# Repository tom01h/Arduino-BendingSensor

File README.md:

# ひずみゲージでスキー板のたわみを測る

[Arduino UNO R4もどきのボードと自作基板](https://github.com/tom01h/RA4M1)を使って実験します

事情あって、センサー部分は実際にスキー場で使っているものですが、制御部分はスキー場で使っているものとは別のものです

センサー部分は[ひずみゲージ](https://ja.aliexpress.com/item/1005003672107724.html)（BX120-100AA）と[HX711](https://ja.aliexpress.com/item/1005004245273524.html)（Mini Board）をちょい変(3.3V化)したものを使います

## Arduinoもどき

制御には[Arduino UNO R4もどきのボードと自作基板](https://github.com/tom01h/RA4M1)を使います

D5端子がクロック、D2,D3,D4端子がデータ入力端子です

プログラムは`BendingSensor.ino`です  
LCDに計測値を表示するためにu8g2ライブラリを使います

1秒に10回計測値を表示、最初の10回はゼロキャリブレーションに使います

### ピン配置
下の絵ではJ5,J9がDATA0(D4)で、絵には無いけどJ10,J11がDATA1(D3)でJ15,J16がDATA2(D2)です  
それぞれ、どちらか一方のコネクタを使います

## センサー

### HX711を改造する
3.3Vに対応するために[ここ](https://kohacraft.com/archives/202103201133.html)の真似をして改造します  
(合成抵抗違うくね？って気はしますが…)  
とっても細かい作業です

2個のひずみゲージと組み合わせてホイートストンブリッジを作るための基板が`hx711.kicad_XX`です  
切り取って使います  
0.8mm厚で作りました  
あまり良くないと言われている基板同士のはんだ付け

### 回路
(E+)-(A+)間にひずみゲージを表向きに、(E+)-(A-)間にひずみゲージを裏向きに、(A+)-(E-)と(A-)-(E-)間は固定の抵抗(120Ω)をつなぎます  
2枚使っているのは温度補償のため  
スキー板の表裏に貼るわけにもいかないので、間に挟んだ0.4mm厚のプラバンに瞬間接着剤で固定しています  
それ以外の部分は大体でついていればよいので両面テープで固定しています

### 設計図（のようなもの）
断面図

センサー部分は上から
- 100mm x 15mm のプラバン（0.4mm厚）
- 両面テープ
- ひずみゲージ（表）
- 瞬間接着剤
- 100mm x 15mm のプラバン（0.4mm厚）
- 瞬間接着剤
- ひずみゲージ（裏）
- 両面テープ
- 135mm x 15mm のプラバン（0.4mm厚）

HX711をプラバンに止めているのは1.2mm厚の両面テープ

センサー部分の平面図

### 組み立て
古い写真です
#### センサー部分

#### センサーとHX711接続
下の写真はHX711基板は裏返った状態

#### ケーブルの加工

4芯のケーブルは[これ](https://ja.aliexpress.com/item/4000570401041.html)の`AWG28 4Core`を使っているのだけど、ちょっと固すぎな気がします  
センサー（HX711）側は外皮（黒いの）2㎝だけむいて、中の線は5mmだけむいています  
外皮をむくのには[これ](https://ja.aliexpress.com/item/1005005504458064.html)を使っています  

制御基板側は長めに外皮（黒いの）をむいて、熱収縮チューブで保護しています  
コネクタは[これ](https://ja.aliexpress.com/item/1005003757087073.html)の4P  
Groveコネクタっぽい見た目ですが、電源とGNDを逆にするという致命的な間違いをしています。今更直せないのでこのままいきますが…  

#### ケーブルに接続
1枚目が表から見た絵で2枚目が裏から見た絵

#### ホットボンド

#### 熱収縮チューブ

長さ16㎝に切った直径12mmの[熱収縮チューブ](https://ja.aliexpress.com/item/32838965930.html)`12mm`を全体の保護に使います  
アイロンで加熱しますが、加熱しすぎに注意！！

↑をチューブでくるむと↓になる

## 後処理

実際にスキー場で使うとノイズとドリフトがひどいのでバンドパスフィルターで後処理します  
後処理でドリフト消すなら温度補償いらなかったのでは？とも思いますが…

```
import numpy as np
from scipy import signal
from scipy import stats

略

    #バターワースフィルタ（バンドパス）
    def bandpass(x, samplerate, fp, fs, gpass, gstop):
        fn = samplerate / 2                               #ナイキスト周波数
        wp = fp / fn                                      #ナイキスト周波数で通過域端周波数を正規化
        ws = fs / fn                                      #ナイキスト周波数で阻止域端周波数を正規化
        N, Wn = signal.buttord(wp, ws, gpass, gstop)      #オーダーとバターワースの正規化周波数を計算
        b, a = signal.butter(N, Wn, "band")               #フィルタ伝達関数の分子と分母を計算
        y = signal.filtfilt(b, a, x)                      #信号に対してフィルタをかける
        return y

略

    samplerate = 10
    gpass = 3    #通過域端最大損失[dB]
    gstop = 40   #阻止域端最小損失[dB]

    # バンドパス
    fp = np.array([0.06, 2])   # 通過域端周波数[Hz]
    fs = np.array([0.03, 4])   # 阻止域端周波数[Hz]
    for i in range(6):
        x=y[i]
        y[i] = bandpass(x, samplerate, fp, fs, gpass, gstop)

    # 正規化
    for i in range(6):
        x=y[i]
        y[i] = stats.zscore(x)
```

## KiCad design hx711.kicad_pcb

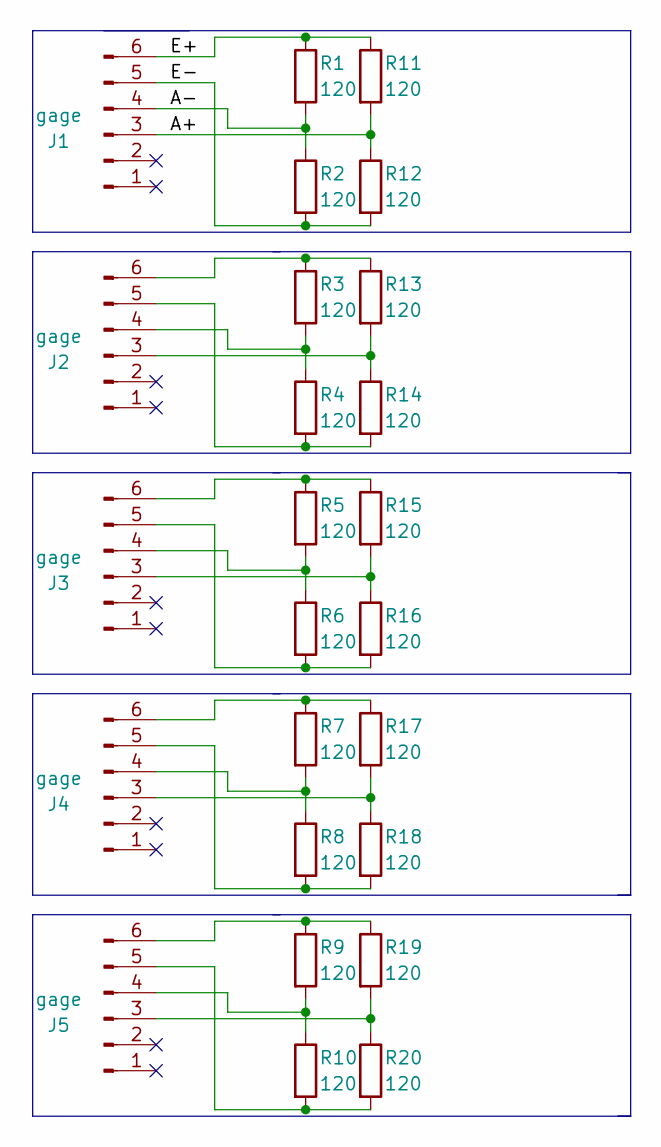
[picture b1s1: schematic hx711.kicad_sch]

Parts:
J1, J2, J3, J4, J5: gage; PinHeader_1x06_P2.54mm_Vertical
R1, R2, R3, R4, R5, R6, R7, R8, R9, R10, R11, R12, R13, R14, R15, R16, R17, R18, R19, R20: 120; R_1206_3216Metric_Pad1.30x1.75mm_HandSolder

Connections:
/A+: J1.3, R11.2, R12.1
/A-: J1.4, R1.2, R2.1
/E+: J1.6, R1.1, R11.1
/E-: J1.5, R2.2, R12.2
unnamed: J2.3, R13.2, R14.1
unnamed: J2.4, R3.2, R4.1
unnamed: J2.5, R4.2, R14.2
unnamed: J2.6, R3.1, R13.1
unnamed: J3.3, R15.2, R16.1
unnamed: J3.4, R5.2, R6.1
unnamed: J3.5, R6.2, R16.2
unnamed: J3.6, R5.1, R15.1
unnamed: J4.3, R17.2, R18.1
unnamed: J4.4, R7.2, R8.1
unnamed: J4.5, R8.2, R18.2
unnamed: J4.6, R7.1, R17.1
unnamed: J5.3, R19.2, R20.1
unnamed: J5.4, R9.2, R10.1
unnamed: J5.5, R10.2, R20.2
unnamed: J5.6, R9.1, R19.1

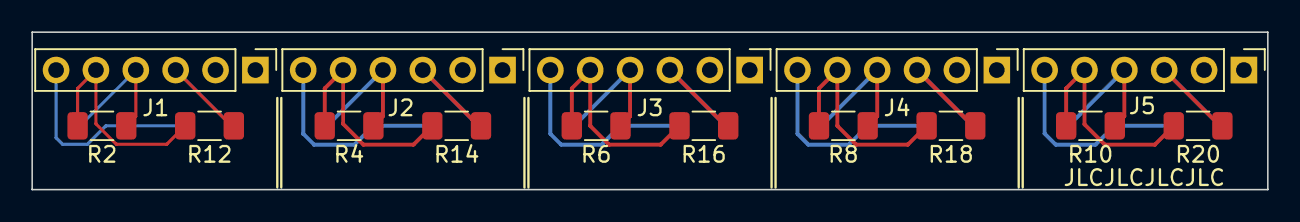
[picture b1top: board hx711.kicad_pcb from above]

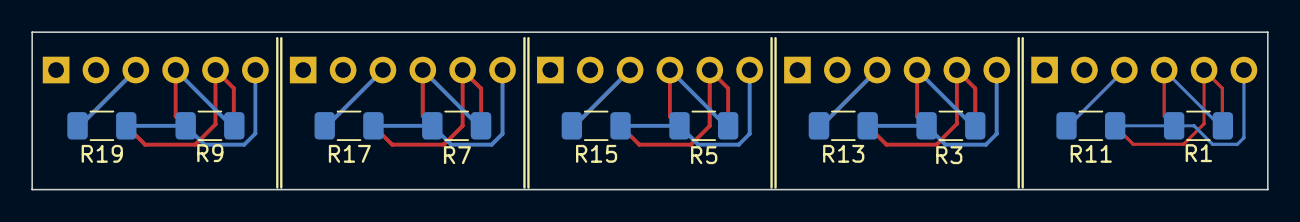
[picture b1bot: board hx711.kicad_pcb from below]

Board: 2 copper layers, 78.7 x 10.0 mm, 25 parts (10 on the bottom side), 20 nets.

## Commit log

2024-02-04 Initial
2024-04-06 芯材挟んだ
